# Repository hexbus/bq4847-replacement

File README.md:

# BQ4847 Replacement Module

**Drop-in replacement for the BQ4847Y DIP RTC chip using the BQ4802Y for 5V legacy systems.**  
Maintains full functionality with modern, readily available components.

---

## PCB ordering

- **[Download the Gerber ZIP](https://github.com/hexbus/bq4847-replacement/raw/refs/heads/main/gerbers.zip)**
- **[Open JLCPCB using my referral link](https://jlcpcb.com/?from=RVDYTTLKZHK)**

Download the Gerber ZIP, open JLCPCB through the referral link, and upload the ZIP.

Confirm the detected outline, dimensions and layer count, and use this project's documented board and assembly requirements before ordering.

The referral link does not upload files automatically. I may receive referral rewards for qualifying new users.

## Table of Contents

- [PCB ordering](#pcb-ordering)
- [Overview](#overview)
- [Photos](#photos)
  - [Assembled Replacement Module](#assembled-replacement-module)
  - [BQ4802Y Module (Modern)](#bq4802y-module-modern)
  - [BQ4847Y Chip (Original)](#bq4847y-chip-original)
- [Project Status](#project-status)
- [Bill of Materials (BOM)](#bill-of-materials-bom)
- [Installation Instructions](#installation-instructions)
  - [TI-99/4A IDE Card](#bq4852-ti99-ide-card)
- [License](#license)
- [Author](#author)

---

## Overview

Many legacy computer systems used the BQ4847 real-time clock (RTC) chip—an integrated lithium coin-cell battery-backed chip with a typical 10-year lifespan. Today, most of thee original chips are well beyond their intended service life.

This project provides a drop-in replacement using the newer BQ4802Y clock chip. It includes support for a replaceable 3V CR2032 battery via an XH 2-pin connector. Note that while the original BQ4847 supported an external 512K SRAM module, this project does **not** include that memory. However, the BQ4802Y can still manage external SRAM if present.

This design was created specifically for use in the [TI-99/4A IDE Card](http://www.mainbyte.com/ti99/ide_card/ide_card.html), which has a dedicated footprint for the BQ4847.

---

## Photos

### Assembled Replacement Module  

### BQ4802Y Module (Modern)  

### BQ4847Y Chip (Original)  

---

## Project Status

🛠️ **Current Status: Prototype phase**  
This design has not yet been tested in hardware. Boards are on order and manual builds are pending.

---

## Bill of Materials (BOM)

| Component                 | Description                                      | Est. Cost (USD) | Source/Link |
|--------------------------|--------------------------------------------------|------------------|-------------|
| PCB                      | Found in `gerbers.zip` in this repo              | —                | —           |
| BQ4802Y RTC chip         | Main RTC IC                                      | ~$6.25           | [Mouser](https://www.mouser.com/ProductDetail/Texas-Instruments/BQ4802YPW?qs=YxwvVplHM%2FnrYmh0JbPldA%3D%3D) |
| 32.768 kHz Crystal       | Standard watch crystal for RTC - 8mm tall        | $0.20–$0.40      | Mouser       |
| 5K Resistor              | Pull-up resistor - 1/4W 5%                        | ~$0.10           | Mouser       |
| Round Pin Headers        | For DIP socket compatibility                     | ~$0.50           | Various      |
| XH 2 pin 2.54mm header   | For hooking up 3V battery & holder (male/female) | $1.00/ea         | [Example](https://www.amazon.com/JST-XH-2-54mm-Connector-Silicone-Cables/dp/B0D6KSMK1Q/) |
| Battery holder - CR2032  | Battery holder w/switch & CR2032 - Backup        | $2.00/ea         | [Example](https://www.amazon.com/Alinan-Button-Battery-Storage-Container/dp/B09KTVG1Y5) |

---

## Installation Instructions

### BQ4852 TI99 IDE Card

Many early TI-99/4A IDE cards were populated with the **BQ4852**, a combination real-time clock (RTC) and 512K SRAM chip with an internal, non-replaceable battery. At this point, most of these batteries are long dead.

These instructions assume you're replacing the BQ4852 with a modern alternative (the one from this repo) using the other supported clock header on the IDE card—the **BQ4802** in the **BQ4847-compatible socket**. Unlike the BQ4852, the BQ4802 (and most other supported options) do **not** include integrated SRAM. To maintain compatibility, the card’s [original designer](https://www.unige.ch/medecine/nouspikel/ti99/ide2.htm) included a footprint at **IC23** to add external 512K SRAM.

If you're installing a clock chip **without built-in SRAM**, you'll need to populate IC23 with a compatible SRAM chip. The following steps walk through the full replacement process.

---

1. **Remove the Original BQ4852**  
   Carefully remove the BQ4852 from **IC27** by pulling it straight up. This removes both the clock and built-in SRAM.

2. **Install External SRAM**  
   Populate **IC23** with a [512Kx8 SRAM chip](https://www.mouser.com/ProductDetail/727-CY2148ELL45ZSXIT).

3. **Install Required Capacitors**  
   Solder two [0805 0.1uf surface-mount capacitors](https://www.mouser.com/ProductDetail/KEMET/C0805C104M5RAC7210?qs=sGAEpiMZZMvsSlwiRhF8qsKzCboK%252BzaMcQGghezj1XY%3D):
   - **C23** — decoupling for the SRAM at IC23
   - **C25** — decoupling for the new clock chip at the BQ4847 socket

4. **Insert the BQ4802 Clock Chip Assembly**  
   Insert the BQ4802 Kit Assembly into the **BQ4847 socket**:
   - Align the dot on the chip with the notch in the silkscreen (facing **C25** and the top edge of the IDE card).
   - The crystal and resistor should be installed just above the chip.

5. **Attach and Secure the [Battery Holder](https://www.amazon.com/Alinan-Button-Battery-Storage-Container/dp/B09KTVG1Y5?th=1)**  
   - Connect a CR2032 battery holder to the 2-pin XH 2.54mm female header and insulate appropriately.
   - Ensure correct polarity (**+ on the left**, per the silkscreen).
   - Mount the battery holder securely nearby using double-sided tape.
   - Leave the **battery switch OFF** during initial testing.

6. **Set the IDE Card Switch**  
   - Set the rear **IDE switch** to the **OFF** position (usually the center setting).

7. **Power On the System**  
   - Power on your **Peripheral Expansion System (PEB)**.
   - Power on your **TI-99/4A** and wait for the Master Title Screen.
   - Flip the IDE card’s switch to **TI** (if using a TI-compatible configuration).

8. **Load the IDE DSR**  
   - Run `IDELOAD` to detect and initialize the IDE card’s DSR (Device Service Routine).
   - The best way to load the DSR is via the 64K cartridge image (loaded in a FinalGROM, FlashROM99, UberGROM, or Guidry 64K cartridge board).  This binary is located in the idedsr_v17.zip as of the writing of this readme, [on this page.](https://hexbus.com/ti99geek/Projects/idedsr/idedsr.html#idedsr)
    
9. **Test Battery Backup Functionality**  
   - If the DSR loads successfully:
     - Turn the **battery switch ON**.
     - Power down the system, then power it back up.
     - In BASIC, run `CALL IDEST` or `CALL IDETD` to verify the date and time were retained.

10. **Troubleshooting Tips**  
    - If the DSR does not load or the clock fails to retain time:
      - Recheck all IC placements and capacitor installations.
      - Use a multimeter to verify connectivity and power.
      - Confirm the DSR is still present by rerunning `IDELOAD`.
      - Make sure you have the current version of the IDE DSR, and follow the troubleshooting steps [here](https://hexbus.com/ti99geek/Projects/idedsr/idedsr.html#idedsr).
      - Seek help via community resources like the [TI-99/4A Forum on AtariAge](https://forums.atariage.com/forum/164-ti-994a-computers/).

---

## License

This project is open hardware. You are free to use, modify, and distribute it, ideally with attribution. Please see the license file in this repo.

---

## Author

Designed by [hexbus](https://github.com/hexbus).

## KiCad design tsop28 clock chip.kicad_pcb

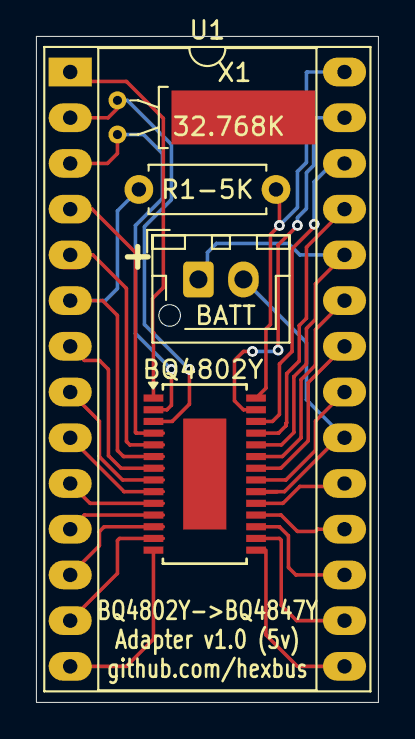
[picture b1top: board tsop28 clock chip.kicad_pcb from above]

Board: 2 copper layers, 19.0 x 37.0 mm, 5 parts (0 on the bottom side), 28 nets.

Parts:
32.768K: 5K; R_Axial_DIN0207_L6.3mm_D2.5mm_P7.62mm_Horizontal
BATT: JST_XH_B2B-XH-AM_1x02_P2.50mm_Vertical
BQ4802Y: TSSOP-28-1EP_4.4x9.7mm_P0.65mm
U1: DIP-28_W15.24mm_Socket_LongPads
X1: 32.768K; Crystal_C38-LF_D3.0mm_L8.0mm_Horizontal_1EP_style1

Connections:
1: BQ4802Y.1, U1.1
2: BQ4802Y.3, U1.2, X1.2
3: BQ4802Y.2, U1.3, X1.1
4: BQ4802Y.4, U1.4
5: BQ4802Y.5, U1.5
6: 32.768K.1, BQ4802Y.6, U1.6
7: BQ4802Y.7, U1.7
8: BQ4802Y.8, U1.8
9: BQ4802Y.9, U1.9
10: BQ4802Y.10, U1.10
11: BQ4802Y.11, U1.11
12: BQ4802Y.12, U1.12
13: BQ4802Y.13, U1.13
14: BQ4802Y.14, U1.14
15: BQ4802Y.15, U1.15
16: BQ4802Y.16, U1.16
17: BQ4802Y.17, U1.17
18: BQ4802Y.18, U1.18
19: BQ4802Y.19, U1.19
20: BATT.2, BQ4802Y.20, U1.20
21: BQ4802Y.21, U1.21
22: BQ4802Y.22, U1.22
23: BQ4802Y.23, U1.23
24: BATT.1, BQ4802Y.24, U1.24
25: BQ4802Y.25, U1.25
26: BQ4802Y.26, U1.26
27: BQ4802Y.27, U1.27
28: 32.768K.2, BQ4802Y.28, U1.28

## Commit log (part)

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2025-07-28 Create LICENSE
2025-07-28 Update LICENSE
